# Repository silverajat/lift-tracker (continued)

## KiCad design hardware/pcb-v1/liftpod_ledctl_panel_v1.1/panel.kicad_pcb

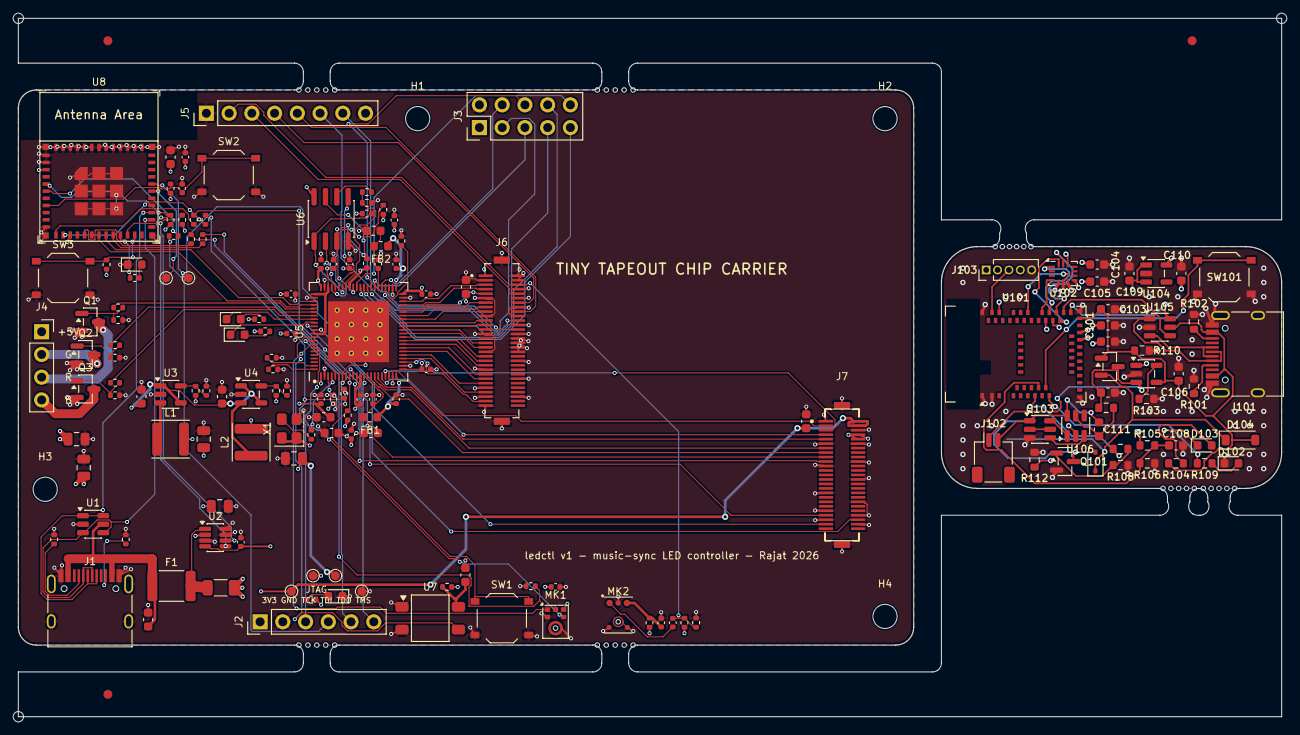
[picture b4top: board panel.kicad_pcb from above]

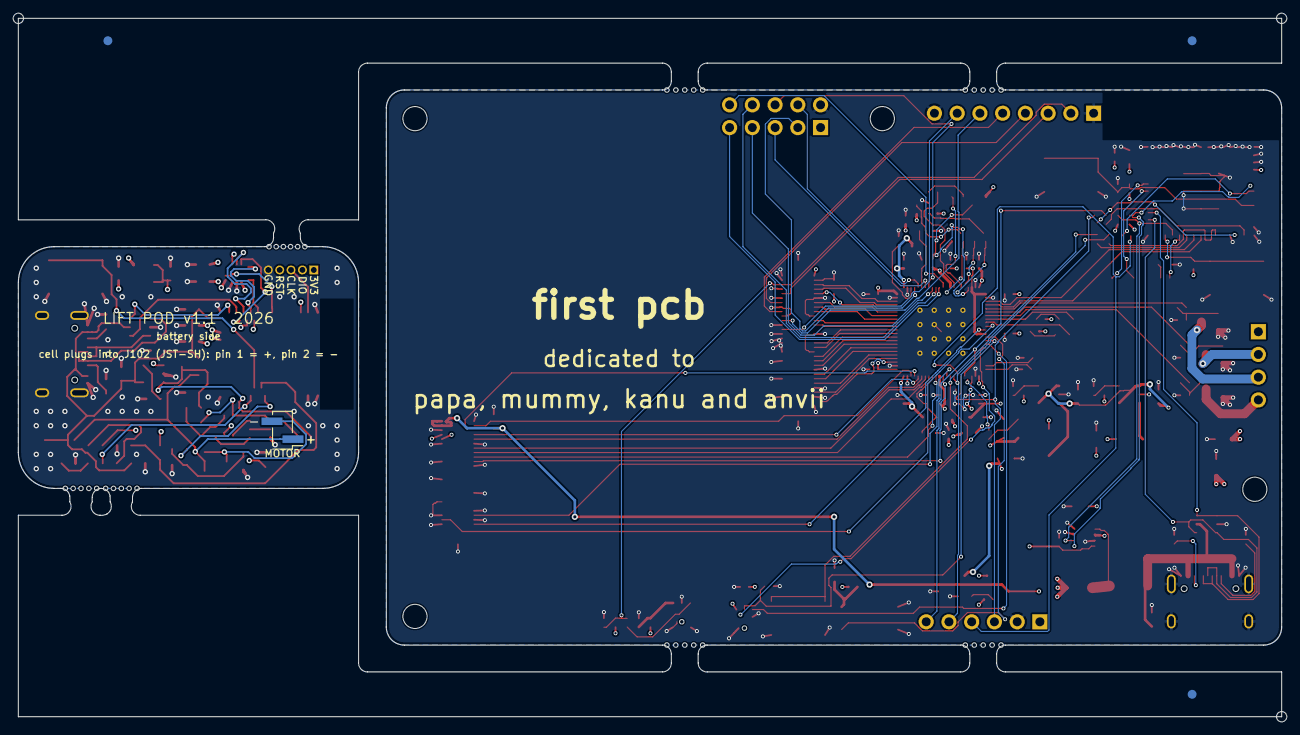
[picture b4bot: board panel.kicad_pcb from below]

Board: 4 copper layers, 141.1 x 78.0 mm, 209 parts (4 on the bottom side), 148 nets.

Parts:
C1, C4, C6, C34, C35, C36: 10u; C_0603_1608Metric
C2, C9, C11, C12, C13, C14, C15, C17, C18, C19, C20, C21, C22, C23, C24, C26, C27, C30, C37: 100n; C_0402_1005Metric
C3, C5, C7, C28, C29: 22u; C_0805_2012Metric
C8, C10, C16, C25, C31: 4.7u; C_0603_1608Metric
C32, C33, C38: 1u; C_0402_1005Metric
C101: 10uF; C_0603_1608Metric
C102, C104, C105, C108, C111: 100nF; C_0603_1608Metric
C103, C106, C107, C109, C110: 4.7uF; C_0603_1608Metric
D1: green PWR; LED_0603_1608Metric
D2: yellow LED0; LED_0603_1608Metric
D3: yellow LED1; LED_0603_1608Metric
D4: blue ESP; LED_0603_1608Metric
D101: 1N4148WS; D_SOD-323
D102: GREEN; LED_0603_1608Metric
D103: RED; LED_0603_1608Metric
D104: B5819W; D_SOD-123
F1: 2.6A hold / 5A trip; Fuse_1812_4532Metric
FB1, FB2: 600R@100MHz; L_0603_1608Metric
H1, H2, H3, H4: M2.5; MountingHole_2.7mm_M2.5
J1: USB-C (power + ESP32 USB); USB_C_Receptacle_HRO_TYPE-C-31-M-12
J2: FPGA JTAG; PinHeader_1x06_P2.54mm_Vertical
J3: FPGA expansion; PinHeader_2x05_P2.54mm_Vertical
J4: LED strip (1=+5V black, 2=G, 3=R, 4=B); PinSocket_1x04_P2.54mm_Vertical
J5: Analog pins (scope / external mic); PinHeader_1x08_P2.54mm_Vertical
J6: DF12NB(5.0)-60DP-0.5V(51); Hirose_DF12NB5.0-60DP_TT
J7: DF12NB(5.0)-50DP-0.5V(51); Hirose_DF12NB5.0-50DP_TT
J101: USB-C; USB_C_Receptacle_HRO_TYPE-C-31-M-12
J102: JST-SH BATT; JST_SH_SM02B-SRSS-TB_1x02-1MP_P1.00mm_Horizontal
J103: SWD; PinHeader_1x05_P1.27mm_Vertical
J104: MOTOR; PinHeader_1x02_P2.00mm_Vertical_SMD_Pin1Left
KiKit_FID_B_1, KiKit_FID_B_2, KiKit_FID_B_3: Fiducial
KiKit_FID_T_1, KiKit_FID_T_2, KiKit_FID_T_3: Fiducial
KiKit_MB_1_1, KiKit_MB_1_2, KiKit_MB_1_3, KiKit_MB_1_4, KiKit_MB_1_5, KiKit_MB_2_1, KiKit_MB_2_2, KiKit_MB_2_3, KiKit_MB_2_4, KiKit_MB_2_5, KiKit_MB_3_1, KiKit_MB_3_2, KiKit_MB_3_3, KiKit_MB_3_4, KiKit_MB_3_5, KiKit_MB_4_1, KiKit_MB_4_2, KiKit_MB_4_3, KiKit_MB_4_4, KiKit_MB_4_5, KiKit_MB_5_1, KiKit_MB_5_2, KiKit_MB_5_3, KiKit_MB_5_4, KiKit_MB_5_5, KiKit_MB_5_6, KiKit_MB_6_1, KiKit_MB_6_2, KiKit_MB_6_3, KiKit_MB_6_4, KiKit_MB_6_5, KiKit_MB_7_1, KiKit_MB_7_2, KiKit_MB_7_3, KiKit_MB_7_4, KiKit_MB_7_5: NPTH
KiKit_TO_1, KiKit_TO_2, KiKit_TO_3: NPTH
L1, L2: 2.2uH SWPA4030S2R2MT; L_Sunlord_SWPA4030S
MK1: ICS-43434; InvenSense_ICS-43434-6_3.5x2.65mm
MK2: MSM381A3729Z9E-C; MEMSensing_LGA-6_2.95x3.76mm
Q1, Q2, Q3, Q101: AO3400A; SOT-23
Q102: AO3401A; SOT-23
Q103: FS8205A; SOT-23-6
R1, R2: 5.1k; R_0402_1005Metric
R3: 10m 1%; R_1206_3216Metric
R4: 2.2k; R_0402_1005Metric
R5: 68k; R_0402_1005Metric
R6, R8: 15k; R_0402_1005Metric
R7, R13, R33, R34: 10k; R_0402_1005Metric
R9, R10, R18, R19, R20, R25, R26, R27, R35, R36: 4.7k; R_0402_1005Metric
R11, R12, R14, R15, R17, R42: 1k; R_0402_1005Metric
R16: 0; R_0402_1005Metric
R21: 22; R_0402_1005Metric
R22, R23, R24, R29, R30, R37, R38, R39, R40, R41: 100; R_0402_1005Metric
R28, R31, R32: 100k; R_0402_1005Metric
R101, R102: 5.1k; R_0603_1608Metric
R103: 15k; R_0603_1608Metric
R104, R112: 1k; R_0603_1608Metric
R105, R106: 1M; R_0603_1608Metric
R107, R111: 100; R_0603_1608Metric
R108, R110: 100k; R_0603_1608Metric
R109: 330; R_0603_1608Metric
SW1: RECONFIG; SW_Push_1P1T_XKB_TS-1187A
SW2: ESP RESET; SW_Push_1P1T_XKB_TS-1187A
SW3: ESP BOOT; SW_Push_1P1T_XKB_TS-1187A
SW101: USER; SW_Push_1P1T_XKB_TS-1187A
TP1: +5V; TestPoint_Pad_D1.0mm
TP2: +3V3; TestPoint_Pad_D1.0mm
TP3: +1V0; TestPoint_Pad_D1.0mm
TP4: GND; TestPoint_Pad_D1.0mm
TP5: ESP RXD0; TestPoint_Pad_D1.0mm
TP6: ESP TXD0; TestPoint_Pad_D1.0mm
U1, U105: USBLC6-2SC6; SOT-23-6
U2: INA219AIDCNR; SOT-23-8
U3: SY8089AAAC 3V3; SOT-23-5
U4: SY8089AAAC 1V0; SOT-23-5
U5: GW2AR-LV18QN88C8/I7; QFN-88-1EP_10x10mm_P0.4mm_EP6.74x6.74mm
U6: W25Q16JVSNIQ; SOIC-8_3.9x4.9mm_P1.27mm
U7: IRM-H638T/TR2; Everlight_IRM-H6xxT
U8: ESP32-C3-MINI-1-N4; ESP32-C3-MINI-1
U101: MDBT50Q-1MV2; Raytac_MDBT50Q
U102: BMI270; Bosch_LGA-14_3x2.5mm_P0.5mm
U103: MCP73831-2-OT; SOT-23-5
U104: ME6211C33M5G; SOT-23-5
U106: DW01A; SOT-23-6
X1: 27MHz 3.3V CMOS; Oscillator_SMD_Abracon_ASE-4Pin_3.2x2.5mm

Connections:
Board_0-+1V0: C7.1, C12.1, C13.1, C14.1, C15.1, C16.1, FB1.1, FB2.1, L2.2, R7.1, TP3.1, U5.1, U5.22, U5.45, U5.66
Board_0-+3V3: C2.1, C5.1, C17.1, C18.1, C19.1, C20.1, C21.1, C22.1, C23.1, C24.1, C25.1, C26.1, C27.1, C30.1, C34.1, C36.1, C37.1, J2.1, J3.1, J6.1, J7.8, J7.10, L1.2, MK1.5, R4.1, R5.1, R9.1, R14.1, R15.1, R18.1, R19.1, R20.1, R29.1, R30.1, R31.1, R33.1, R34.1, R35.1, R36.1, TP2.1, U2.4, U5.3, U5.12, U5.23, U5.44, U5.58, U5.64, U5.67, U5.78, U6.8, U8.3, X1.1, X1.4
Board_0-+5V: C3.1, C4.1, C6.1, C28.1, C29.1, C35.1, J4.1, J7.2, J7.4, R3.2, TP1.1, U2.2, U3.1, U3.4, U4.1, U4.4
Board_0-+5V_F: F1.2, R3.1, U2.1
Board_0-CLK27_RAW: R21.1, X1.3
Board_0-ESP_BOOT: R34.2, SW3.1, U8.23
Board_0-ESP_EN: C38.1, R33.2, SW2.1, U8.8
Board_0-ESP_LED: R42.1, U8.21
Board_0-ESP_LED_R: D4.2, R42.2
Board_0-ESP_RECONFIG: R41.1, U8.20
Board_0-ESP_RXD0: TP5.1, U8.30
Board_0-ESP_TCK: R38.1, U8.13
Board_0-ESP_TDI: R39.1, U8.6
Board_0-ESP_TDO: R40.1, U8.16
Board_0-ESP_TMS: R37.1, U8.12
Board_0-ESP_TXD0: TP6.1, U8.31
Board_0-EXP_IO48: J3.3, U5.48
Board_0-EXP_IO49: J3.4, U5.49
Board_0-EXP_IO51: J3.5, U5.51
Board_0-EXP_IO52: J3.6, U5.52
Board_0-EXP_IO53: J3.7, U5.53
Board_0-EXP_IO54: J3.8, U5.54
Board_0-EXP_IO55: J3.9, U5.55
Board_0-EXP_IO56: J3.10, U5.56
Board_0-FB_1V0: R7.2, R8.1, U4.5
Board_0-FB_3V3: R5.2, R6.1, U3.5
Board_0-FL_CLK: R16.1, R17.1, U5.59
Board_0-FL_CLK_FLASH: R16.2, U6.6
Board_0-FL_CS: R18.2, U5.60, U6.1
Board_0-FL_HOLD: R20.2, U5.63, U6.7
Board_0-FL_MISO: U5.62, U6.2
Board_0-FL_MOSI: U5.61, U6.5
Board_0-FL_WP: R19.2, U5.57, U6.3
Board_0-FPGA_CLK27: R21.2, U5.4
Board_0-FPGA_EXTR: R13.1, U5.47
Board_0-FPGA_LED0: D2.1, U5.74
Board_0-FPGA_LED1: D3.1, U5.75
Board_0-FPGA_MODE0: R11.1, U5.88
Board_0-FPGA_MODE1: R12.1, U5.87
Board_0-FPGA_RECONFIG_N: R9.2, R41.2, SW1.1, U5.9
Board_0-FPGA_TCK: J2.3, R10.1, R38.2, U5.6
Board_0-FPGA_TDI: J2.4, R39.2, U5.7
Board_0-FPGA_TDO: J2.5, R40.2, U5.8
Board_0-FPGA_TMS: J2.6, R37.2, U5.5
Board_0-FPGA_UART_RX: U5.70, U8.18
Board_0-FPGA_UART_TX: U5.69, U8.19
Board_0-GATE_B: Q3.1, R24.2, R27.1
Board_0-GATE_G: Q2.1, R23.2, R26.1
Board_0-GATE_R: Q1.1, R22.2, R25.1
Board_0-GND: C1.2, C2.2, C3.2, C4.2, C5.2, C6.2, C7.2, C8.2, C9.2, C10.2, C11.2, C12.2, C13.2, C14.2, C15.2, C16.2, C17.2, C18.2, C19.2, C20.2, C21.2, C22.2, C23.2, C24.2, C25.2, C26.2, C27.2, C28.2, C29.2, C30.2, C31.2, C32.2, C34.2, C35.2, C36.2, C37.2, C38.2, D1.1, D4.1, J1.A1, J1.A12, J1.B1, J1.B12, J1.S1, J2.2, J3.2, J5.1, J5.8, J6.2, J6.3, J6.4, J6.8, J6.11, J6.12, J6.16, J6.19, J6.20, J6.24, J6.27, J6.28, J6.30, J6.32, J6.34, J6.35, J6.36, J6.40, J6.43, J6.48, J6.51, J6.55, J6.56, J6.59, J6.MP, J7.1, J7.6, J7.11, J7.12, J7.20, J7.21, J7.28, J7.33, J7.38, J7.41, J7.44, J7.45, J7.48, J7.MP, MK1.2, MK1.3, MK2.2, MK2.3, MK2.5, MK2.6, Q1.2, Q2.2, Q3.2, R1.2, R2.2, R6.2, R8.2, R10.2, R11.2, R12.2, R13.2, R17.2, R25.2, R26.2, R27.2, R28.2, R32.2, SW1.2, SW2.2, SW3.2, TP4.1, U1.2, U2.3, U2.7, U2.8, U3.2, U4.2, U5.2, U5.21, U5.24, U5.43, U5.46, U5.65, U5.68, U5.89, U6.4, U7.1, U7.2, U8.1, U8.2, U8.11, U8.14, U8.36, U8.37, U8.38, U8.39, U8.40, U8.41, U8.42, U8.43, U8.44, U8.45, U8.46, U8.47, U8.48, U8.49, U8.50, U8.51, U8.52, U8.53, X1.2
Board_0-I2C_SCL: R35.2, U2.5, U8.5
Board_0-I2C_SDA: R36.2, U2.6, U8.22
Board_0-I2S_SCK: MK1.4, U5.82
Board_0-I2S_SD: MK1.6, R28.1, U5.80
Board_0-I2S_WS: MK1.1, U5.81
Board_0-IR_OUT: U5.79, U7.3
Board_0-IR_VDD: C31.1, R29.2, U7.4
Board_0-LED0_A: D2.2, R14.2
Board_0-LED1_A: D3.2, R15.2
Board_0-LED_PWR_A: D1.2, R4.2
Board_0-LX_1V0: L2.1, U4.3
Board_0-LX_3V3: L1.1, U3.3
Board_0-MICA_OUT: C33.1, MK2.1
Board_0-MICA_VDD: C32.1, MK2.4, R30.2
Board_0-PWM_B: R24.1, U5.73
Board_0-PWM_G: R23.1, U5.72
Board_0-PWM_R: R22.1, U5.71
Board_0-STRIP_B: J4.4, Q3.3
Board_0-STRIP_G: J4.2, Q2.3
Board_0-STRIP_R: J4.3, Q1.3
Board_0-TT_AN0: C33.2, J5.2, J6.6, R31.2, R32.1
Board_0-TT_AN1: J5.3, J6.10
Board_0-TT_AN2: J5.4, J6.14
Board_0-TT_AN3: J5.5, J6.18
Board_0-TT_AN4: J5.6, J6.22
Board_0-TT_AN5: J5.7, J6.26
Board_0-TT_CLK: J6.57, U5.25
Board_0-TT_CTRL_ENA: J7.46, U5.76
Board_0-TT_CTRL_SEL_INC: J7.47, U5.77
Board_0-TT_CTRL_SEL_RST_N: J7.43, U5.10
Board_0-TT_RST_N: J6.53, U5.26
Board_0-TT_UI0: J6.31, U5.34
Board_0-TT_UI1: J6.33, U5.33
Board_0-TT_UI2: J6.37, U5.32
Board_0-TT_UI3: J6.39, U5.31
Board_0-TT_UI4: J6.41, U5.30
Board_0-TT_UI5: J6.45, U5.29
Board_0-TT_UI6: J6.47, U5.28
Board_0-TT_UI7: J6.49, U5.27
Board_0-TT_UIO0: J6.5, U5.42
Board_0-TT_UIO1: J6.7, U5.41
Board_0-TT_UIO2: J6.9, U5.40
Board_0-TT_UIO3: J6.13, U5.39
Board_0-TT_UIO4: J6.15, U5.38
Board_0-TT_UIO5: J6.17, U5.37
Board_0-TT_UIO6: J6.21, U5.36
Board_0-TT_UIO7: J6.23, U5.35
Board_0-TT_UO0: J7.19, U5.11
Board_0-TT_UO1: J7.17, U5.13
Board_0-TT_UO2: J7.15, U5.15
Board_0-TT_UO3: J7.13, U5.16
Board_0-TT_UO4: J7.9, U5.17
Board_0-TT_UO5: J7.7, U5.18
Board_0-TT_UO6: J7.5, U5.19
Board_0-TT_UO7: J7.3, U5.20
Board_0-USB_CC1: J1.A5, R1.1
Board_0-USB_CC2: J1.B5, R2.1
Board_0-USB_DN: J1.A7, J1.B7, U1.3, U1.4, U8.26
Board_0-USB_DP: J1.A6, J1.B6, U1.1, U1.6, U8.27
Board_0-VBUS: C1.1, F1.1, J1.A4, J1.A9, J1.B4, J1.B9, U1.5
Board_0-VCCPLLL: C8.1, C9.1, FB1.2, U5.14
Board_0-VCCPLLR: C10.1, C11.1, FB2.2, U5.50
Board_1-/+3V3: C101.1, C102.1, C104.1, C105.1, C110.1, J103.1, U101.28, U101.30, U102.5, U102.8, U104.5
Board_1-/BATT_N: C111.2, J102.2, Q103.1, U106.6
Board_1-/BUTTON: SW101.1, U101.13
Board_1-/CC1: J101.A5, R101.1
Board_1-/CC2: J101.B5, R102.1
Board_1-/CHG_PROG: R103.1, U103.5
Board_1-/CHG_STAT: D103.1, U103.1
Board_1-/GND: C101.2, C102.2, C103.2, C104.2, C105.2, C106.2, C107.2, C108.2, C109.2, C110.2, D102.1, J101.A1, J101.A12, J101.B1, J101.B12, J101.S1, J103.5, Q101.2, Q103.3, R101.2, R102.2, R103.2, R106.2, R108.2, R110.2, R112.2, SW101.2, U101.1, U101.2, U101.15, U101.33, U101.55, U102.6, U102.7, U103.2, U104.2, U105.2
Board_1-/IMU_CS: U101.38, U102.12
Board_1-/IMU_INT1: U101.41, U102.4
Board_1-/IMU_INT2: U101.44, U102.9
Board_1-/IMU_MISO: U101.39, U102.1
Board_1-/IMU_MOSI: U101.36, U102.14
Board_1-/IMU_SCK: U101.37, U102.13
Board_1-/LED_CHG_A: D103.2, R104.2
Board_1-/LED_USER: R109.1, U101.14
Board_1-/LED_USER_A: D102.2, R109.2
Board_1-/MOTOR_EN: R107.1, U101.10
Board_1-/MOTOR_G: Q101.1, R107.2, R108.1
Board_1-/MOTOR_N: D101.2, J104.2, Q101.3
Board_1-/PROT_D: Q103.2, Q103.5
Board_1-/PROT_OC: Q103.4, U106.3
Board_1-/PROT_OD: Q103.6, U106.1
Board_1-/PROT_VCC: C111.1, R111.2, U106.5
Board_1-/PROT_VM: R112.1, U106.2
Board_1-/SWDCLK: J103.3, U101.53
Board_1-/SWDIO: J103.2, U101.51
Board_1-/SYS: C109.1, D101.1, D104.1, J104.1, Q102.2, U104.1, U104.3
Board_1-/USB_CONN_DM: J101.A7, J101.B7, U105.1
Board_1-/USB_CONN_DP: J101.A6, J101.B6, U105.3
Board_1-/USB_DM: U101.34, U105.6
Board_1-/USB_DP: U101.35, U105.4
Board_1-/VBAT: C107.1, J102.1, Q102.3, R105.1, R111.1, U103.3
Board_1-/VBAT_SENSE: C108.1, R105.2, R106.1, U101.11
Board_1-/VBUS: C103.1, C106.1, D104.2, J101.A4, J101.A9, J101.B4, J101.B9, Q102.1, R104.1, R110.1, U101.32, U103.4, U105.5
Board_1-/nRESET: J103.4, U101.40

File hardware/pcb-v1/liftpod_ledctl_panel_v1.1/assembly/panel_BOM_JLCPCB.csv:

Comment,Designator,Footprint,LCSC Part #
TS-1187A tact switch,"SW1,SW101,SW2,SW3",SW_Push_1P1T_XKB_TS-1187A,C318884
100nF,"C102,C104,C105,C108,C111",C_0603_1608Metric,C14663
100k,"R108,R110",R_0603_1608Metric,C25803
1k,"R11,R12,R14,R15,R17,R42",R_0402_1005Metric,C11702
10u,"C1,C101,C34,C35,C36,C4,C6",C_0603_1608Metric,C19702
4.7k,"R10,R18,R19,R20,R25,R26,R27,R35,R36,R9",R_0402_1005Metric,C25900
JST-SH BATT,J102,JST_SH_SM02B-SRSS-TB_1x02-1MP_P1.00mm_Horizontal,C160402
100n,"C11,C12,C13,C14,C15,C17,C18,C19,C2,C20,C21,C22,C23,C24,C26,C27,C30,C37,C9",C_0402_1005Metric,C1525
5.1k,"R101,R102",R_0603_1608Metric,C23186
4.7uF,"C10,C103,C106,C107,C109,C110,C16,C25,C31,C8",C_0603_1608Metric,C19666
100,"R22,R23,R24,R29,R30,R37,R38,R39,R40,R41",R_0402_1005Metric,C25076
yellow LED0,"D2,D3",LED_0603_1608Metric,C72038
GREEN,"D1,D102",LED_0603_1608Metric,C72043
10m 1%,R3,R_1206_3216Metric,C601097
USBLC6-2SC6,"U1,U105",SOT-23-6,C7519
2.2k,R4,R_0402_1005Metric,C25879
AO3400A,"Q1,Q101,Q2,Q3",SOT-23,C20917
15k,"R6,R8",R_0402_1005Metric,C25756
FPGA JTAG,J2,PinHeader_1x06_P2.54mm_Vertical,C42431790
22,R21,R_0402_1005Metric,C25092
330,R109,R_0603_1608Metric,C23138
10k,"R13,R33,R34,R7",R_0402_1005Metric,C25744
2.2uH SWPA4030S2R2MT,"L1,L2",L_Sunlord_SWPA4030S,C36409
DW01A,U106,SOT-23-6,C351410
ESP32-C3-MINI-1-N4,U8,ESP32-C3-MINI-1,C2838502
DF12NB(5.0)-60DP-0.5V(51),J6,Hirose_DF12NB5.0-60DP_TT,C2847989
22u,"C28,C29,C3,C5,C7",C_0805_2012Metric,C45783
MDBT50Q-1MV2,U101,Raytac_MDBT50Q,C5118826
BMI270,U102,Bosch_LGA-14_3x2.5mm_P0.5mm,C2836813
1u,"C32,C33,C38",C_0402_1005Metric,C52923
RED,D103,LED_0603_1608Metric,C2286
ICS-43434,MK1,InvenSense_ICS-43434-6_3.5x2.65mm,C5656610
15k,R103,R_0603_1608Metric,C22809
1N4148WS,D101,D_SOD-323,C2128
USB-C,"J1,J101",USB_C_Receptacle_HRO_TYPE-C-31-M-12,C165948
1k,"R104,R112",R_0603_1608Metric,C21190
2.6A hold / 5A trip,F1,Fuse_1812_4532Metric,C20814
FS8205A,Q103,SOT-23-6,C2830320
"LED strip (1=+5V black, 2=G, 3=R, 4=B)",J4,PinSocket_1x04_P2.54mm_Vertical,C2718488
5.1k,"R1,R2",R_0402_1005Metric,C25905
INA219AIDCNR,U2,SOT-23-8,C87469
MCP73831-2-OT,U103,SOT-23-5,C424093
GW2AR-LV18QN88C8/I7,U5,QFN-88-1EP_10x10mm_P0.4mm_EP6.74x6.74mm,C380550
blue ESP,D4,LED_0603_1608Metric,C72041
SY8089AAAC 1V0,"U3,U4",SOT-23-5,C78988
1M,"R105,R106",R_0603_1608Metric,C22935
B5819W,D104,D_SOD-123,C8598
100k,R28,R_0402_1005Metric,C25741
ME6211C33M5G,U104,SOT-23-5,C82942
W25Q16JVSNIQ,U6,SOIC-8_3.9x4.9mm_P1.27mm,C2456211
600R@100MHz,"FB1,FB2",L_0603_1608Metric,C1002
68k,R5,R_0402_1005Metric,C36871
100,"R107,R111",R_0603_1608Metric,C22775
DF12NB(5.0)-50DP-0.5V(51),J7,Hirose_DF12NB5.0-50DP_TT,C3020266
AO3401A,Q102,SOT-23,C15127
IRM-H638T/TR2,U7,Everlight_IRM-H6xxT,C91447
0,R16,R_0402_1005Metric,C17168
MSM381A3729Z9E-C,MK2,MEMSensing_LGA-6_2.95x3.76mm,C51928206
27MHz 3.3V CMOS,X1,Oscillator_SMD_Abracon_ASE-4Pin_3.2x2.5mm,C22434870

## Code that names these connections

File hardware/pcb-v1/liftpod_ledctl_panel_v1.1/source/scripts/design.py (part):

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    # ---- IMU: BMI270 on SPI (BMI160 symbol: same LGA-14 pinout) ----------
    dict(ref="U2", sym=("Sensor_Motion", "BMI160"), value="BMI270",
         fp="Package_LGA:Bosch_LGA-14_3x2.5mm_P0.5mm", lcsc="C2836813",
         pins={"1": "IMU_MISO",    # SDO
               "2": NC,            # ASDx: aux I2C unused; datasheet allows floating
               "3": NC,            # ASCx: aux I2C unused; datasheet allows floating
               "4": "IMU_INT1", "5": "+3V3", "6": "GND", "7": "GND", "8": "+3V3",
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    # ESD protection on the USB data lines and VBUS
    dict(ref="U5", sym=("Power_Protection", "USBLC6-2SC6"), value="USBLC6-2SC6",
         fp="Package_TO_SOT_SMD:SOT-23-6", lcsc="C7519",
         pins={"1": "USB_CONN_DM", "6": "USB_DM", "3": "USB_CONN_DP", "4": "USB_DP",
               "2": "GND", "5": "VBUS"}),

    # ---- Charger: MCP73831-2 (4.2 V), 15k PROG = ~67 mA (0.5C for 140 mAh)
    dict(ref="U3", sym=("Battery_Management", "MCP73831-2-OT"), value="MCP73831-2-OT",
         fp="Package_TO_SOT_SMD:SOT-23-5", lcsc="C424093",
         pins={"1": "CHG_STAT", "2": "GND", "3": "VBAT", "4": "VBUS", "5": "CHG_PROG"}),
    dict(ref="R3", sym=("Device", "R"), value="15k", fp="Resistor_SMD:R_0603_1608Metric",
         lcsc="C22809", pins={"1": "CHG_PROG", "2": "GND"}),
    dict(ref="C6", sym=("Device", "C"), value="4.7uF", fp="Capacitor_SMD:C_0603_1608Metric",
         lcsc="C19666", pins={"1": "VBUS", "2": "GND"}),
    dict(ref="C7", sym=("Device", "C"), value="4.7uF", fp="Capacitor_SMD:C_0603_1608Metric",
         lcsc="C19666", pins={"1": "VBAT", "2": "GND"}),
    # charge LED: on while charging (STAT pulls low)
    dict(ref="R4", sym=("Device", "R"), value="1k", fp="Resistor_SMD:R_0603_1608Metric",
         lcsc="C21190", pins={"1": "VBUS", "2": "LED_CHG_A"}),
    dict(ref="D3", sym=("Device", "LED"), value="RED", fp="LED_SMD:LED_0603_1608Metric",
         lcsc="C2286", pins={"2": "LED_CHG_A", "1": "CHG_STAT"}),

    # ---- Battery ----------------------------------------------------------
    # Keyed JST-SH 1.0 mm socket: the cell plugs in, can't go in backwards.
    # Pin 1 = cell +, pin 2 = cell - (BATT_N, before the protection FETs).
    dict(ref="J2", sym=("Connector_Generic", "Conn_01x02"), value="JST-SH BATT",
         fp="Connector_JST:JST_SH_SM02B-SRSS-TB_1x02-1MP_P1.00mm_Horizontal", lcsc="C160402",
         pins={"1": "VBAT", "2": "BATT_N"}),
    # Battery protection (DW01A + FS8205A), the same circuit as inside a
    # protected cell, so the board is safe with any cell: cuts off at
    # 4.3 V (overcharge), 2.5 V (over-discharge), ~3 A (overcurrent/short).
    # The FETs sit in the cell's negative lead: cell - = BATT_N, board GND = pack -.
    dict(ref="U6", sym=("Battery_Management", "DW01A"), value="DW01A",
         fp="Package_TO_SOT_SMD:SOT-23-6", lcsc="C351410",
         pins={"1": "PROT_OD", "2": "PROT_VM", "3": "PROT_OC", "4": NC,
               "5": "PROT_VCC", "6": "BATT_N"}),
    dict(ref="Q3", sym=("gympod", "FS8205A"), value="FS8205A",
         fp="Package_TO_SOT_SMD:SOT-23-6", lcsc="C2830320",
         pins={"1": "BATT_N", "2": "PROT_D", "3": "GND", "4": "PROT_OC",
               "5": "PROT_D", "6": "PROT_OD"}),
    dict(ref="R11", sym=("Device", "R"), value="100", fp="Resistor_SMD:R_0603_1608Metric",
         lcsc="C22775", pins={"1": "VBAT", "2": "PROT_VCC"}),
    dict(ref="C11", sym=("Device", "C"), value="100nF", fp="Capacitor_SMD:C_0603_1608Metric",
         lcsc="C14663", pins={"1": "PROT_VCC", "2": "BATT_N"}),
    dict(ref="R12", sym=("Device", "R"), value="1k", fp="Resistor_SMD:R_0603_1608Metric",
         lcsc="C21190", pins={"1": "PROT_VM", "2": "GND"}),
    # battery voltage sense: 1M/1M divider -> AIN0, 100 nF for the ADC sample
    dict(ref="R5", sym=("Device", "R"), value="1M", fp="Resistor_SMD:R_0603_1608Metric",
         lcsc="C22935", pins={"1": "VBAT", "2": "VBAT_SENSE"}),
    dict(ref="R6", sym=("Device", "R"), value="1M", fp="Resistor_SMD:R_0603_1608Metric",
         lcsc="C22935", pins={"1": "VBAT_SENSE", "2": "GND"}),
    dict(ref="C8", sym=("Device", "C"), value="100nF", fp="Capacitor_SMD:C_0603_1608Metric",
         lcsc="C14663", pins={"1": "VBAT_SENSE", "2": "GND"}),

    # ---- 3.3 V regulator: ME6211C33 LDO from the battery -----------------
    dict(ref="U4", sym=("Regulator_Linear", "ME6211C33M5"), value="ME6211C33M5G",
         fp="Package_TO_SOT_SMD:SOT-23-5", lcsc="C82942",
         pins={"1": "SYS", "3": "SYS", "2": "GND", "4": NC, "5": "+3V3"}),
    dict(ref="C9", sym=("Device", "C"), value="4.7uF", fp="Capacitor_SMD:C_0603_1608Metric",
         lcsc="C19666", pins={"1": "SYS", "2": "GND"}),
    dict(ref="C10", sym=("Device", "C"), value="4.7uF", fp="Capacitor_SMD:C_0603_1608Metric",
         lcsc="C19666", pins={"1": "+3V3", "2": "GND"}),

    # ---- Vibration motor driver (motor runs from VBAT) --------------------
    dict(ref="Q1", sym=("Transistor_FET", "AO3400A"), value="AO3400A",
         fp="Package_TO_SOT_SMD:SOT-23", lcsc="C20917",
         pins={"1": "MOTOR_G", "2": "GND", "3": "MOTOR_N"}),
    dict(ref="R7", sym=("Device", "R"), value="100", fp="Resistor_SMD:R_0603_1608Metric",
         lcsc="C22775", pins={"1": "MOTOR_EN", "2": "MOTOR_G"}),
    dict(ref="R8", sym=("Device", "R"), value="100k", fp="Resistor_SMD:R_0603_1608Metric",
         lcsc="C25803", pins={"1": "MOTOR_G", "2": "GND"}),   # keeps the motor off at boot
    dict(ref="D1", sym=("Device", "D"), value="1N4148WS", fp="Diode_SMD:D_SOD-323",
         lcsc="C2128", pins={"1": "SYS", "2": "MOTOR_N"}),   # flyback
    dict(ref="J4", sym=("Connector_Generic", "Conn_01x02"), value="MOTOR",
         fp="Connector_PinHeader_2.00mm:PinHeader_1x02_P2.00mm_Vertical_SMD_Pin1Left", lcsc=None, dnp=True,
         pins={"1": "SYS", "2": "MOTOR_N"}),

    # ---- Load sharing: USB powers the system when plugged in, so the charger
    # only sees the battery and can terminate. Unplugged: Q2 turns on
    # (gate pulled to GND) and the battery feeds SYS through it.
    dict(ref="Q2", sym=("Transistor_FET", "AO3401A"), value="AO3401A",
         fp="Package_TO_SOT_SMD:SOT-23", lcsc="C15127",
         pins={"1": "VBUS", "2": "SYS", "3": "VBAT"}),      # G, S, D
    dict(ref="D4", sym=("Device", "D_Schottky"), value="B5819W",
         fp="Diode_SMD:D_SOD-123", lcsc="C8598",
         pins={"1": "SYS", "2": "VBUS"}),                   # K, A
    dict(ref="R10", sym=("Device", "R"), value="100k", fp="Resistor_SMD:R_0603_1608Metric",
         lcsc="C25803", pins={"1": "VBUS", "2": "GND"}),    # Q2 gate pull-down

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         fp="Button_Switch_SMD:SW_Push_1P1T_XKB_TS-1187A", lcsc="C318884",
         pins={"1": "BUTTON", "2": "GND"}),
    dict(ref="R9", sym=("Device", "R"), value="330", fp="Resistor_SMD:R_0603_1608Metric",
         lcsc="C23138", pins={"1": "LED_USER", "2": "LED_USER_A"}),
    dict(ref="D2", sym=("Device", "LED"), value="GREEN", fp="LED_SMD:LED_0603_1608Metric",
         lcsc="C72043", pins={"2": "LED_USER_A", "1": "GND"}),

    # ---- SWD programming header (first flash with a debug probe) ----------
    dict(ref="J3", sym=("Connector_Generic", "Conn_01x05"), value="SWD",
         fp="Connector_PinHeader_1.27mm:PinHeader_1x05_P1.27mm_Vertical", lcsc=None, dnp=True,
         pins={"1": "+3V3", "2": "SWDIO", "3": "SWDCLK", "4": "nRESET", "5": "GND"}),


    # ---- Power flags (tell ERC these nets are driven) ----------------------
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    dict(ref="#FLG02", sym=("power", "PWR_FLAG"), value="PWR_FLAG", fp="", lcsc=None,
         pins={"1": "VBUS"}, virtual=True),
    dict(ref="#FLG03", sym=("power", "PWR_FLAG"), value="PWR_FLAG", fp="", lcsc=None,
         pins={"1": "SYS"}, virtual=True),
    # the cell (via J2) drives these two
    dict(ref="#FLG04", sym=("power", "PWR_FLAG"), value="PWR_FLAG", fp="", lcsc=None,
         pins={"1": "BATT_N"}, virtual=True),
    dict(ref="#FLG05", sym=("power", "PWR_FLAG"), value="PWR_FLAG", fp="", lcsc=None,
         pins={"1": "PROT_VCC"}, virtual=True),
]

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
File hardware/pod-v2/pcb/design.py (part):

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    charger's centre magnet. The pod can sit either way round, so the pads
    feed a bridge rectifier (4x B5819WS Schottky) into VCHG, with a TVS on VCHG. The
    bridge diodes also steer ESD on the exposed pads into that TVS. The
    charger's STAT pin (CHG_STAT) tells the nRF it's on the charger.
  - No button (tap gestures from the IMU), no load-sharing path (the pod
    isn't used while it charges), no JST socket (cell wires solder to pads).
  - New: 2 MB SPI flash (USON 2x3) for recordings, sharing the IMU's SPI bus.
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         fp="lift:Ebyte_E73-2G4M08S1C", lcsc="C356849", unused_nc=True,
         pins={"5": "GND", "21": "GND",              # 24 (GND) is an inner pad: left open, 5 + 21 ground the module
               "19": "+3V3", "23": "+3V3",            # VDD, VDDH tied: normal-voltage mode
               "15": "SPI_SCK", "13": "SPI_MOSI", "11": "SPI_MISO",   # order matches the IMU's pins
               "10": "IMU_CS", "9": "IMU_INT1", "33": "FLASH_CS",
               "17": "MOTOR_EN", "35": "CHG_STAT", "7": "LED",
               "8": "VBAT_SENSE",                     # P0.29 = AIN5
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    # ---- IMU: ST LSM6DSV16X on SPI (LSM6DSL symbol: same LGA-14 pinout) ----
    dict(ref="U2", sym=("Sensor_Motion", "LSM6DSL"), value="LSM6DSV16X",
         fp="Package_LGA:LGA-14_3x2.5mm_P0.5mm_LayoutBorder3x4y", lcsc="C5267406",
         pins={"1": "SPI_MISO",    # SDO/SA0
               "2": "GND", "3": "GND",   # SDx/SCx: analog hub/Qvar unused -> GND (datasheet)
               "4": "IMU_INT1", "5": "+3V3", "6": "GND", "7": "GND", "8": "+3V3",
               "9": NC, "10": NC, "11": NC,   # INT2 unused (INT1 does wake + taps); OCS_Aux/SDO_Aux open
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    # ---- 2 MB flash for recordings, on the IMU's SPI bus ---------------------
    dict(ref="U7", sym=("Memory_Flash", "W25Q32JVSS"), value="W25Q16JVUXIQ",
         fp="lift:Winbond_USON-8-1EP_2x3mm_P0.5mm", lcsc="C2843335",
         pins={"1": "FLASH_CS", "2": "SPI_MISO", "3": "+3V3", "4": "GND",
               "5": "SPI_MOSI", "6": "SPI_SCK", "7": "+3V3", "8": "+3V3"}),
    dict(ref="C14", sym=("Device", "C"), value="100nF", fp=C0402,
         lcsc="C1525", pins={"1": "+3V3", "2": "GND"}),
    # both chips share the bus: keep both deselected until the firmware runs
    dict(ref="R13", sym=("Device", "R"), value="100k", fp=R0402,
         lcsc="C25741", pins={"1": "+3V3", "2": "FLASH_CS"}),
    dict(ref="R14", sym=("Device", "R"), value="100k", fp=R0402,
         lcsc="C25741", pins={"1": "+3V3", "2": "IMU_CS"}),

    # ---- Charging input: Fitbit Air charger, either polarity ---------------
    # Pads on the underside (B.Cu). Full bridge of 1N5819-class Schottkys:
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    # ~0.8 V, which would leave the charger in dropout around 4.0 V.)
    dict(ref="J1", sym=("Connector_Generic", "Conn_01x02"), value="CHARGER",
         fp="lift:Charger_Contacts_FitbitAir_P18mm", lcsc=None, dnp=True,
         pins={"1": "CH_A", "2": "CH_B"}),
    dict(ref="D6", sym=("Device", "D_Schottky"), value="B5819WS",
         fp="Diode_SMD:D_SOD-323", lcsc="C22624",
         pins={"1": "VCHG", "2": "CH_A"}),                    # K, A: pad A -> VCHG
    dict(ref="D7", sym=("Device", "D_Schottky"), value="B5819WS",
         fp="Diode_SMD:D_SOD-323", lcsc="C22624",
         pins={"1": "CH_A", "2": "GND"}),                     # GND -> pad A
    dict(ref="D8", sym=("Device", "D_Schottky"), value="B5819WS",
         fp="Diode_SMD:D_SOD-323", lcsc="C22624",
         pins={"1": "VCHG", "2": "CH_B"}),                    # pad B -> VCHG
    dict(ref="D9", sym=("Device", "D_Schottky"), value="B5819WS",
         fp="Diode_SMD:D_SOD-323", lcsc="C22624",
         pins={"1": "CH_B", "2": "GND"}),                     # GND -> pad B
    dict(ref="D5", sym=("Device", "D_Zener"), value="ESD5Z5.0T1G",
         fp="Diode_SMD:D_SOD-523", lcsc="C82044",
         pins={"1": "VCHG", "2": "GND"}),                    # unidirectional TVS: K, A
    dict(ref="U3", sym=("Battery_Management", "MCP73831-2-OT"), value="MCP73831-2-OT",
         fp="Package_TO_SOT_SMD:SOT-23-5", lcsc="C424093",
         pins={"1": "CHG_STAT", "2": "GND", "3": "VBAT", "4": "VCHG", "5": "CHG_PROG"}),
    dict(ref="R3", sym=("Device", "R"), value="47k", fp=R0402,
         lcsc="C25792", pins={"1": "CHG_PROG", "2": "GND"}),
    dict(ref="C6", sym=("Device", "C"), value="4.7uF", fp=C0402,
         lcsc="C23733", pins={"1": "VCHG", "2": "GND"}),
    dict(ref="C7", sym=("Device", "C"), value="4.7uF", fp=C0402,
         lcsc="C23733", pins={"1": "VBAT", "2": "GND"}),
    # charge LED: on while charging (STAT pulls low), works with a flat cell too
    dict(ref="R4", sym=("Device", "R"), value="1k", fp=R0402,
         lcsc="C11702", pins={"1": "VCHG", "2": "LED_CHG_A"}),
    dict(ref="D3", sym=("Device", "LED"), value="RED", fp="LED_SMD:LED_0603_1608Metric",
         lcsc="C2286", pins={"2": "LED_CHG_A", "1": "CHG_STAT"}),

    # ---- Battery: cell wires solder to 2 top pads (cell sits on top) ----------------------
    # Pad + = VBAT, pad - = GND. The cell MUST have its own protection board
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         pins={"1": "VBAT", "2": "GND"}),
    # battery voltage sense: 1M/1M -> AIN0 (2 uA), 100 nF holds it for the ADC
    dict(ref="R5", sym=("Device", "R"), value="1M", fp=R0402,
         lcsc="C26083", pins={"1": "VBAT", "2": "VBAT_SENSE"}),
    dict(ref="R6", sym=("Device", "R"), value="1M", fp=R0402,
         lcsc="C26083", pins={"1": "VBAT_SENSE", "2": "GND"}),
    dict(ref="C8", sym=("Device", "C"), value="100nF", fp=C0402,
         lcsc="C1525", pins={"1": "VBAT_SENSE", "2": "GND"}),

    # ---- 3.3 V: XC6206 LDO from the battery (~1 uA quiescent) --------------
    dict(ref="U4", sym=("Regulator_Linear", "XC6206PxxxMR"), value="XC6206P332MR",
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    # ---- Vibration motor (coin ERM on top of the board, wires to 2 pads) ----
    dict(ref="Q1", sym=("Transistor_FET", "AO3400A"), value="AO3400A",
         fp="Package_TO_SOT_SMD:SOT-23", lcsc="C20917",
         pins={"1": "MOTOR_G", "2": "GND", "3": "MOTOR_N"}),
    dict(ref="R7", sym=("Device", "R"), value="100", fp=R0402,
         lcsc="C25076", pins={"1": "MOTOR_EN", "2": "MOTOR_G"}),
    dict(ref="R8", sym=("Device", "R"), value="100k", fp=R0402,
         lcsc="C25741", pins={"1": "MOTOR_G", "2": "GND"}),   # motor off at boot
    dict(ref="D1", sym=("Device", "D"), value="1N4148WS", fp="Diode_SMD:D_SOD-323",
         lcsc="C2128", pins={"1": "MOTOR_N", "2": "VBAT"}),   # ERM motor: either way round; + side faces the power parts   # flyback
    dict(ref="J4", sym=("Connector_Generic", "Conn_01x02"), value="MOTOR",
         fp="lift:Motor_Pads_2x1.2x1.6mm_P2.5mm", lcsc=None, dnp=True,
         pins={"1": "MOTOR_N", "2": "VBAT"}),   # ERM motor: either way round; + side faces the power parts

    # ---- Status LED (shines through a light pipe in the lid) -----------------
    dict(ref="R9", sym=("Device", "R"), value="330", fp=R0402,
         lcsc="C25104", pins={"1": "LED", "2": "LED_A"}),
    dict(ref="D2", sym=("Device", "LED"), value="GREEN", fp="LED_SMD:LED_0603_1608Metric",
         lcsc="C12624", pins={"2": "LED_A", "1": "GND"}),

    # ---- SWD: 3 test pads on the underside (cover with kapton; reflash anytime) -----
    dict(ref="J3", sym=("Connector_Generic", "Conn_01x03"), value="SWD",
         fp="lift:SWD_Pads_1x03_P1.5mm", lcsc=None, dnp=True,
         pins={"1": "SWDIO", "2": "SWDCLK", "3": "GND"}),

    # ---- Power flags (tell ERC these nets are driven) ----------------------
    dict(ref="#FLG01", sym=("power", "PWR_FLAG"), value="PWR_FLAG", fp="", lcsc=None,
         pins={"1": "GND"}, virtual=True),
    # VCHG is driven by the charger through the bridge D6/D7
    dict(ref="#FLG03", sym=("power", "PWR_FLAG"), value="PWR_FLAG", fp="", lcsc=None,
         pins={"1": "VCHG"}, virtual=True),
]

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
